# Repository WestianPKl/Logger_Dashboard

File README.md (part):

# 🌡️ IoT Logger Dashboard

A full-stack IoT monitoring platform for collecting, visualizing, and managing environmental sensor data from distributed devices. The system integrates custom-built hardware (ESP32, STM32, MicroPython nodes) with a modern web dashboard, communicating over MQTT and WebSockets for real-time data streaming.

---

## 📋 Table of Contents

- [Overview](#overview)
- [Architecture](#architecture)
- [Technology Stack](#technology-stack)
- [Features](#features)
- [Project Structure](#project-structure)
- [Backend](#backend)
- [Frontend](#frontend)
- [Logger Firmware](#logger-firmware)
- [Database](#database)
- [Authentication & Authorization](#authentication--authorization)
- [MQTT Communication](#mqtt-communication)
- [Hardware](#hardware)
- [Getting Started](#getting-started)
- [Environment Variables](#environment-variables)
- [API Reference](#api-reference)
- [Testing](#testing)

---

## Overview

IoT Logger Dashboard is designed to monitor environmental conditions (temperature, humidity, atmospheric pressure, altitude, voltage) across multiple locations. Sensor nodes deployed in buildings collect data and transmit it via MQTT to a centralized backend. Users interact with the system through a responsive web dashboard that provides real-time charts, floor plan visualizations, equipment management, and a full role-based administration panel.

**Key metrics:**

- 380+ tracked devices (loggers, sensors, relays)
- 247,000+ recorded measurements
- 12 measurement parameter types
- Multi-location, multi-floor support
- 90 concurrent database connections
- 4 JWT token types for layered security

---

## Architecture

```
┌──────────────────┐      MQTT       ┌──────────────────┐     HTTP/WS     ┌──────────────────┐
│   Sensor Nodes   │ ──────────────► │     Backend      │ ◄────────────── │    Frontend      │
│                  │                 │                  │ ──────────────► │                  │
│  ESP32 + STM32   │  devices/+/    │  Express.js 5.2  │   Socket.io     │  React 19 + TS   │
│  MicroPython     │  status        │  Sequelize ORM   │   4.8           │  MUI 7 + Redux   │
│  SHT40 / BME280  │                │  MQTT Client     │                 │  ECharts + XYFlow│
│  PCF8563T RTC    │  ◄──────────── │  Socket.io 4.8   │                 │  RTK Query       │
│                  │  devices/      │  Sharp + Multer  │                 │  Vite 7.3 (SWC)  │
│                  │  {id}/cmd      │  Nodemailer      │                 │                  │
└──────────────────┘                 └────────┬─────────┘                 └──────────────────┘
                                              │
                                     ┌────────▼─────────┐
                                     │   MySQL 9.x DB   │
                                     │  14 tables       │
                                     │  5 views         │
                                     │  Pool: 90 conn   │
                                     └──────────────────┘
```

---

## Technology Stack

### Backend

| Technology        | Version    | Purpose                                    |
| ----------------- | ---------- | ------------------------------------------ |
| Node.js           | ES Modules | Runtime environment                        |
| Express.js        | 5.2.1      | HTTP framework                             |
| Sequelize         | 6.37.7     | MySQL ORM with transactions & soft deletes |
| mysql2            | 3.16.1     | MySQL driver                               |
| Socket.io         | 4.8.3      | Real-time WebSocket communication          |
| MQTT.js           | 5.14.1     | IoT message broker client                  |
| JSON Web Token    | 9.0.3      | Authentication (4 token types)             |
| express-validator | 7.3.1      | Request body validation                    |
| bcryptjs          | 3.0.3      | Password hashing                           |
| Sharp             | 0.34.5     | Image processing & WebP conversion         |
| Multer            | 2.0.2      | File upload handling (500KB limit)         |
| Nodemailer        | 7.0.12     | Email via Gmail SMTP (password reset)      |
| Morgan            | 1.10.1     | HTTP access logging                        |
| Compression       | 1.8.1      | Gzip response compression                  |
| uuid              | 13.0.0     | Unique filename generation                 |
| dotenv            | 17.2.3     | Environment variable management            |
| Jest              | 30.2.0     | Testing framework                          |
| Supertest         | 7.2.2      | HTTP integration testing                   |
| ESLint + Prettier | —          | Code quality & formatting                  |

### Frontend

| Technology          | Version | Purpose                            |
| ------------------- | ------- | ---------------------------------- |
| React               | 19.2.3  | UI framework                       |
| TypeScript          | 5.9.3   | Type safety                        |
| Vite                | 7.3.1   | Build tool (SWC transpiler)        |
| Material UI (MUI)   | 7.3.7   | Component library                  |
| MUI X Data Grid     | 8.26.0  | Advanced sortable/paginated tables |
| Redux Toolkit       | 2.11.2  | State management with RTK Query    |
| React Redux         | 9.2.0   | React-Redux bindings               |
| React Router        | 7.13.0  | Client-side routing with loaders   |
| Socket.io Client    | 4.8.3   | Real-time device updates           |
| ECharts             | 3.0.6   | Time-series data visualization     |
| XYFlow (React Flow) | 12.10.0 | Graph / flow diagrams              |
| Styled Components   | 6.3.8   | CSS-in-JS styling                  |
| Emotion             | 11.14.0 | MUI styling engine                 |
| xlsx                | 0.18.5  | Excel spreadsheet generation       |
| file-saver          | 2.0.5   | Client-side file download          |
| jwt-decode          | 4.0.0   | Client-side JWT inspection         |

### Embedded / Logger

| Technology                        | Purpose                                      |
| --------------------------------- | -------------------------------------------- |
| ESP32 (MicroPython)               | Main IoT gateway — WiFi, MQTT, UART to STM32 |
| STM32L476RG / STM32F412RG (CMSIS) | Low-level sensor hub — bare-metal C with DMA |
| MicroPython (generic)             | Standalone sensor nodes — HTTP POST to API   |
| PlatformIO                        | STM32 build & flash toolchain                |
| KiCad                             | PCB schematic & layout design                |

### Sensors & Peripherals

| Component     | Type       | Measurements / Function                               |
| ------------- | ---------- | ----------------------------------------------------- |
| SHT30 / SHT40 | I2C sensor | Temperature (-40–125°C), Humidity (0–100%)            |
| BME280        | I2C sensor | Temperature, Humidity, Atmospheric Pressure, Altitude |
| PCF8563T      | I2C RTC    | Real-Time Clock with battery backup                   |
| I2C LCD       | Display    | Sensor readings & status display                      |
| RGB LEDs      | Output     | Status indication (PWM, 0–65535 range)                |
| Relay module  | Output     | 4-channel relay control (pins 12–15)                  |
| Buzzer        | Output     | Audible alerts on threshold breach                    |
| Push Buttons  | Input      | User interaction (debounced, long-press 3s)           |

---

## Features

- **Real-Time Monitoring** — Live sensor data via MQTT → Socket.io WebSocket pipeline with per-logger events
- **Interactive Charts** — Time-series visualization with ECharts, range selection, and XLSX export
- **Floor Plan Visualization** — Upload floor plan images, place loggers with x/y positioning and zoom control
- **Multi-Location Support** — Organize devices by house → floor → logger hierarchy
- **Equipment Inventory** — Full CRUD for loggers, sensors, relays with soft delete and restore
- **Device Telemetry** — Track firmware/hardware versions, serial numbers, build dates, IP address, last seen
- **Sensor Capability Mapping** — Many-to-many mapping of sensors to data definition parameters
- **Role-Based Access Control** — Three-dimensional permission matrix: functionality × object × access level
- **Superuser Override** — Superuser flag bypasses all permission checks
- **User Management** — Registration, login, avatar upload with Sharp WebP conversion, password reset via Gmail SMTP
- **Data Export** — Export sensor data to XLSX spreadsheets with pivot view support
- **Error Tracking** — Log device and system errors with type (Equipment/DB/Other) and severity (Critical→Info)
- **Equipment Event Logs** — Track STATUS, DATA, OTA, ERROR events per device
- **Process Management** — Define and manage operational process types and definitions
- **Audit Trail** — `created_by` / `updated_by` user tracking on all key entities
- **OTA Support** — Custom UART bootloader for STM32 firmware updates (app at `0x08008000`)
- **Service Mode** — ESP32 3-hour OTA window for configuration and firmware updates
- **Image Processing** — Automatic thumbnail generation and WebP conversion for avatars and floor plans
- **HTTP Access Logging** — Morgan combined-format logging to `access.log`
- **Gzip Compression** — Response compression via compression middleware
- **Transaction Safety** — Sequelize transactions with rollback on all write operations

---

## Project Structure

```
Logger_Dashboard/
│
├── backend/                    # Node.js Express API server
│   ├── server/
│   │   ├── app.js              # Express app setup, middleware, CORS
│   │   ├── mqttClient.js       # MQTT subscriber & data processing
│   │   ├── api/
│   │   │   ├── controller/     # Request handlers
│   │   │   ├── model/          # Sequelize models
│   │   │   └── routes/         # Express route definitions
│   │   ├── bin/www.js          # HTTP server bootstrap + Socket.io init
│   │   ├── libs/jwtToken.js    # JWT generation (4 token types)
│   │   ├── middleware/
│   │   │   ├── body-validation.js   # Request body validation
│   │   │   ├── file.js              # File upload handling (multer)
│   │   │   ├── jwtValidation.js     # JWT auth + permission checking
│   │   │   └── socket.js           # Socket.io middleware
│   │   └── util/
│   │       ├── database.js          # Sequelize connection config
│   │       ├── nodemailer.js        # Email transport setup
│   │       ├── responseHelper.js    # Standardized API responses
│   │       └── sequelizeTools.js    # Query builder utilities
│   ├── uploads/                # Uploaded files (avatars, floor plans)
│   ├── data.json               # Static configuration data
│   ├── package.json
│   ├── jest.config.js
│   └── eslint.config.js
│
├── frontend/                   # React SPA
│   ├── src/
│   │   ├── App.tsx             # Root component
│   │   ├── main.tsx            # Entry point
│   │   ├── components/         # Reusable UI components
│   │   │   ├── selectors/      # Equipment, sensor, house dropdowns
│   │   │   ├── ui/             # SnackBar, forms, modals
│   │   │   └── scripts/        # API interaction helpers
│   │   ├── modules/            # Feature modules (pages)
│   │   │   ├── admin/          # User/role/permission management
│   │   │   ├── dashboard/      # Real-time overview
│   │   │   ├── data/           # Charts, data tables, layout view
│   │   │   ├── equipment/      # Device inventory
│   │   │   ├── house/          # Location & floor management
│   │   │   ├── user/           # User profile
│   │   │   └── process/        # Process workflows
│   │   ├── router/             # SPA route configuration
│   │   ├── socket/             # Socket.io client setup
│   │   ├── store/              # Redux store (auth, account, app state)
│   │   └── util/               # Theme, API helpers, utilities
│   ├── dist-frontend/          # Production build output
│   ├── package.json
│   ├── vite.config.ts
│   └── tsconfig.json
│
├── logger/                     # Embedded firmware
│   ├── ESP32/                  # ESP32 MicroPython firmware
│   │   ├── main.py             # Boot: WiFi → NTP → MQTT → STM32
│   │   ├── program.py          # Main loop: status/data publishing
│   │   ├── mqtt_simple.py      # Lightweight MQTT client
│   │   ├── wireless.py         # WiFi + NTP connection manager
│   │   ├── stm32_uart.py       # UART bridge to STM32 (115200 baud)
│   │   ├── config.py           # Device configuration (IDs, WiFi, MQTT)
│   │   └── status.json         # Runtime status snapshot
│   ├── Micropython/            # Generic MicroPython sensor nodes
│   │   ├── main.py             # Sensor reading + HTTP POST loop
│   │   ├── config.py           # Node configuration
│   │   ├── sht30.py / sht40.py # Temperature/humidity drivers
│   │   ├── bme280_i2c.py       # Pressure/altitude driver
│   │   ├── i2c_lcd.py          # LCD display driver
│   │   ├── rtc_clock.py        # RTC time management
│   │   └── ...                 # Additional peripheral drivers
│   └── STM32/                  # STM32 bare-metal firmware (C / CMSIS)
│       ├── application/        # Main application (PlatformIO project)
│       │   └── src/            # adc, bme280, sht40, i2c, spi, uart,
│       │                       # lcd, rtc, pcf8563t, dma drivers
│       ├── bootloader/         # UART bootloader for OTA updates
│       │   └── src/            # main.c, uart.c, systick.c
│       ├── production_files/   # Flash programming scripts & binaries
│       ├── STM32F412RGT6/      # Reference docs & alt. target
│       └── STM32L4/            # Reference docs for L476RG
│
├── database/                   # Database setup
│   ├── db.sql                  # Schema: tables, views, indexes
│   └── db_data.sql             # Seed data (types, definitions, roles)
│
├── permissions/
│   └── permissions.json        # Default permission matrix
│
└── docs/                       # Documentation & hardware resources
    ├── LoggerDashboard.postman_collection.json  # API collection
    ├── Cover/PicoLogger/       # 3D-printable enclosures (.stl)
    └── PCB/PicoLogger/         # KiCad PCB designs
        ├── IoT_Logger_B_1.0/
        ├── IoT_Logger_C_1.0/
        ├── Pico_TH_Logger_SMD_PCF8563T_2.1/
        └── Pico_TH_Logger_Relay_SMD_PCF8563T_2.1/
```

---

## Backend

### Express API Server

The backend is a Node.js Express 5.2 server with ES module support. It provides a RESTful API, handles MQTT message ingestion from IoT devices, and broadcasts real-time updates to connected clients via Socket.io.

**Middleware stack (in order):**

1. **CORS** — Configurable origins via `FRONTEND_ORIGIN` env var (comma-separated)
2. **Compression** — Gzip response compression
3. **Morgan** — HTTP access logging (combined format → `access.log`)
4. **Express JSON/URL-encoded** — Body parsing with 10MB limit
5. **Cookie Parser** — Cookie handling
6. **Static Files** — Serves `/uploads` and frontend build (`dist-frontend/`)
7. **JWT Validation** — Bearer token verification on protected routes
8. **Permission Checking** — Granular RBAC enforcement per endpoint

**Route mounting:**

| Mount Path       | Module     |
| ---------------- | ---------- |
| `/api/user`      | User       |
| `/api/data`      | Data       |
| `/api/equipment` | Equipment  |
| `/api/process`   | Process    |
| `/api/house`     | House      |
| `/api/common`    | Error Logs |
| `/api/mqtt`      | MQTT       |
| `/api/adm`       | Admin      |

**Error handling:**

- 404 → `notFound()` for unknown routes
- Global error handler → `internalServerError()`
- In production, unknown routes serve `index.html` (SPA fallback)

**Standardized API response format:**

```json
{
	"success": true,
	"message": "Description of result",
	"data": {}
}
```

**HTTP status code helpers:** `200`, `201`, `204`, `400`, `401`, `403`, `404`, `409`, `422`, `429`, `500`, `503`

### File Upload & Image Processing

| Setting       | Value                                              |
| ------------- | -------------------------------------------------- |
| Max file size | 500 KB                                             |
| MIME types    | `image/png`, `image/jpeg`, `image/jpg`             |
| Storage       | `uploads/` directory                               |
| Filename      | `${uuid()}.${extension}`                           |
| Processing    | Sharp — auto WebP conversion, thumbnail generation |

Image variants stored:

- **Avatars:** `avatar` (thumbnail) + `avatar_big` (full-size)
- **House pictures:** `picture_link` + `picture_link_big`
- **Floor layouts:** `layout` (small) + `layout_big` (full-size)

### MQTT Data Pipeline

When sensor data arrives over MQTT:

1. Message is parsed from the `devices/+/status` topic (QoS 0)
2. Message type is identified: `DATA`, `STATUS`, `ERROR`, or `OTA`
3. Timestamps are normalized to `Europe/Warsaw` timezone (UTC+1/+2)
4. **For DATA messages:**
   - SHT40 readings extracted → `temperature`, `humidity`
   - BME280 readings extracted → `temperature`, `humidity`, `pressure` → `atmPressure`, `altitude`
   - Voltage readings extracted → `vin` array → individual voltage values
   - Each measurement matched to `DataDefinition` by name
   - `DataLogs` record created with value + timestamp
   - `DataLastValue` cache replaced with latest reading
5. **For all messages:** `EquStats` updated (firmware versions, serial numbers, build dates, IP, `last_seen`)
6. Socket.io emits `logger_${loggerId}` event with `'refresh'` payload
7. **For ERROR messages:** `ErrorLog` record created in database

**MQTT connection config:**

```
Reconnect period: 2000ms
Keep-alive: 30s
Clean session: true
```

---

## Frontend

### React SPA

The frontend is a single-page application built with React 19, TypeScript, and Material UI 7. It uses Redux Toolkit with RTK Query for API calls and Socket.io for real-time updates.

**State management (Redux store slices):**

- `accountSlice` — User profile data, avatar
- `authenticateSlice` — JWT tokens, login state, permissions
- `applicationSlice` — Global UI state (snackbar alerts, loading indicators)
- `api` — RTK Query endpoints with auto-caching and tag-based invalidation

**RTK Query features:**

- Auto Bearer token injection from localStorage
- 401 error handling → automatic logout + redirect to `/login`
- Zero retry policy (`maxRetries: 0`)
- Cache tags: User, Equipment, House, Data, Admin (14 tag types)

**Socket.io client:**

- Timeout: 5000ms, reconnection attempts: 3, delay: 1000ms
- Listens to `logger_${loggerId}` events for per-device data refresh

### Routes & Pages

```
/ ........................... Main menu
/login ...................... Login page
/register ................... Registration page
/logout ..................... Logout action
/password-reset ............. Request password reset email
/password-reset/:token ...... Complete password reset

/house ...................... House management
  /house/houses ............. House list & CRUD
  /house/floors ............. Floor list & CRUD
  /house/loggers ............ Logger placement management
/house-details/:houseId ..... Floor plan viewer with logger positions

/equipment .................. Equipment inventory
  Types, vendors, models, equipment CRUD
  Equipment log viewer

/logs/:equLoggerId .......... Equipment event log

/data ....................... Data module
  /data ..................... Data summary & definitions
  /data/data-logger/:id ..... Time-series chart view (ECharts)

/admin-panel ................ Administration
  Functionality, object, access level definitions
  Role & permission management
  User management

/user ....................... User module
  Profile, permissions view, roles
```

**Module views:**

| Module            | Description                                                                      |
| ----------------- | -------------------------------------------------------------------------------- |
| **Dashboard**     | Real-time overview cards with latest device readings                             |
| **Data**          | Time-series charts (ECharts), pivot tables, XLSX export, layout visualization    |
| **Equipment**     | CRUD for devices, vendors, models, types; soft delete/restore; event logs        |
| **House**         | Location CRUD, floor plans with image upload, interactive logger placement       |
| **House Details** | Floor plan viewer with logger positions, floor tree navigation, edit forms       |
| **Admin**         | Functionality/object/access level definitions, role CRUD, permission matrix      |
| **User**          | Login, registration, profile with avatar upload, password reset, permission view |
| **Process**       | Process type & definition management                                             |

### Reusable Components

**18 Select dropdowns:** `HouseSelect`, `HouseFloorSelect`, `EquipmentSelect`, `EquipmentVendorSelect`, `EquipmentTypeSelect`, `EquipmentModelSelect`, `EquipmentLoggerSelect`, `EquipmentSensorSelect`, `DataDefinitionSelect`, `AdminUserSelect`, `AdminAccessLevelSelect`, `AdminFunctionalityDefinitionSelect`, `AdminObjectDefinitionSelect`, and more.

**UI components:** `SnackBar` (alert notifications), `LoadingCircle` (spinner), `Wrapper` (layout), `TabPanel` (tabbed content).

---

## Logger Firmware

### ESP32 (MicroPython) — IoT Gateway

The ESP32 acts as the main IoT gateway, bridging STM32 sensor hardware to the cloud. On boot it:

1. Configures GPIO pins (status LED, STM32 control, power LED)
2. Initializes I2C bus for sensor modules and LCD
3. Connects to WiFi (up to 20 retries, 1s each)
4. Synchronizes time via NTP (UTC+1, max 10 retries)
5. Initializes MQTT connection to the broker
6. Establishes UART communication with the STM32 (115200 baud)
7. Enters the main loop publishing status and sensor data

**GPIO Configuration:**

| Pin | Function          | Mode              |
| --- | ----------------- | ----------------- |
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
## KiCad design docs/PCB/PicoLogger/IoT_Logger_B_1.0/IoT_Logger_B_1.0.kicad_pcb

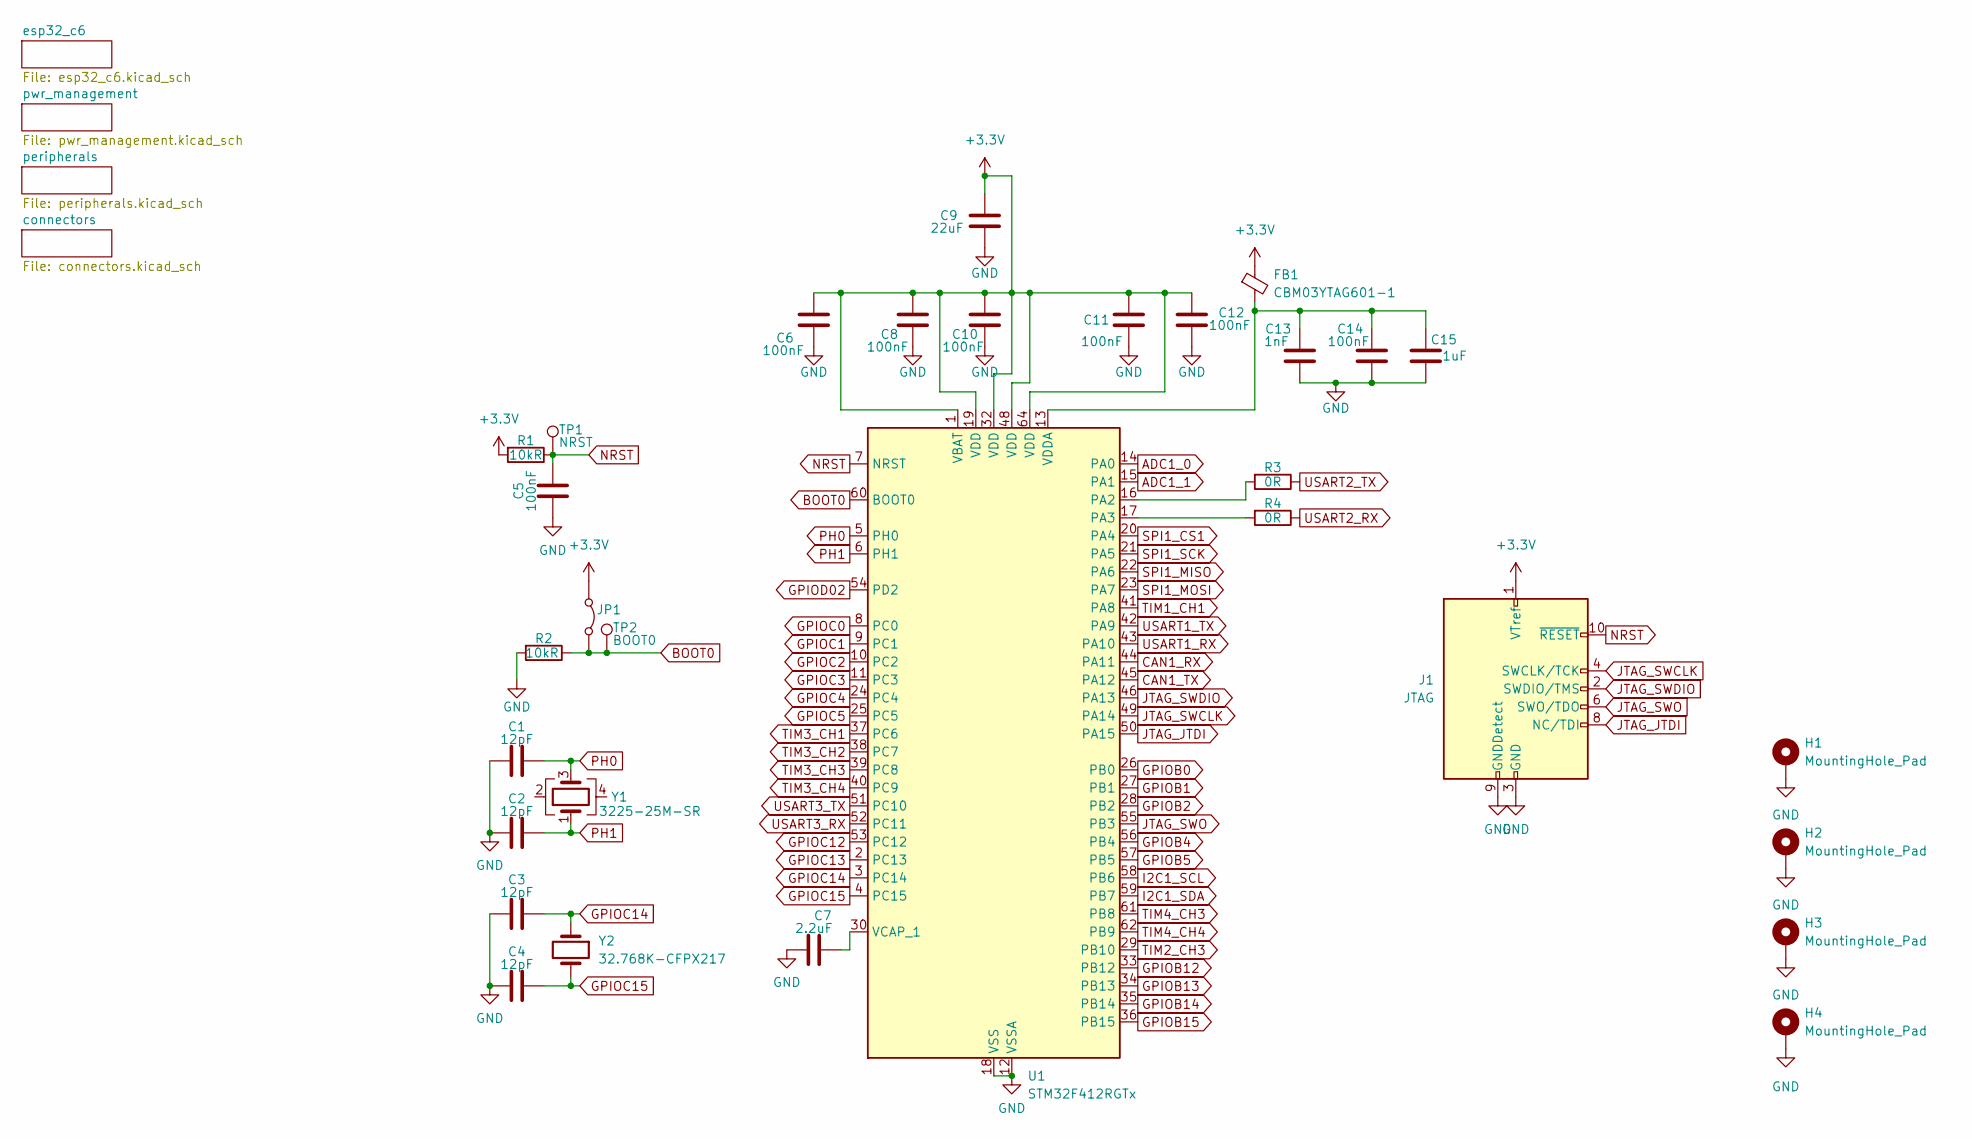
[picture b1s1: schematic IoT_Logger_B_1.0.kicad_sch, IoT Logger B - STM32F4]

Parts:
C1, C2, C3, C4: 12pF; C_0603_1608Metric
C5, C6, C8, C10, C11, C12, C14: 100nF; C_0603_1608Metric
C7: 2.2uF; C_0603_1608Metric
C9: 22uF; C_0603_1608Metric
C13: 1nF; C_0603_1608Metric
C15: 1uF; C_0603_1608Metric
FB1: CBM03YTAG601-1; L_0603_1608Metric
H1, H2, H3, H4: MountingHole_Pad; MountingHole_3.2mm_M3_DIN965_Pad
J1: JTAG; PinHeader_2x05_P1.27mm_Vertical
JP1: Jumper_2_Bridged; PinHeader_1x02_P2.54mm_Vertical
R1, R2: 10kR; R_0603_1608Metric
R3, R4: 0R; R_0603_1608Metric
TP1: NRST; TestPoint_Pad_D1.5mm
TP2: BOOT0; TestPoint_Pad_D1.5mm
U1: STM32F412RGTx; LQFP-64_10x10mm_P0.5mm
Y1: 3225-25M-SR; Crystal_SMD_3225-4Pin_3.2x2.5mm
Y2: 32.768K-CFPX217; Crystal_SMD_3215-2Pin_3.2x1.5mm

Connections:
+3.3V: C6.1, C8.1, C9.1, C10.1, C11.1, C12.1, FB1.1, J1.1 (VTref), JP1.1 (A), R1.2, U1.1 (VBAT), U1.19 (VDD), U1.32 (VDD), U1.48 (VDD), U1.64 (VDD); also elsewhere on the board
ADC1_0: U1.14 (PA0); also elsewhere on the board
ADC1_1: U1.15 (PA1); also elsewhere on the board
BOOT0: JP1.2 (B), R2.1, TP2.1, U1.60 (BOOT0); also elsewhere on the board
CAN1_RX: U1.44 (PA11); also elsewhere on the board
CAN1_TX: U1.45 (PA12); also elsewhere on the board
GND: C1.1, C2.1, C3.1, C4.1, C5.1, C6.2, C7.1, C8.2, C9.2, C10.2, C11.2, C12.2, C13.2, C14.2, C15.2, H1.1, H2.1, H3.1, H4.1, J1.3 (GND), J1.5 (GND), J1.9 (GNDDetect), R2.2, U1.12 (VSSA), U1.18 (VSS), U1.31 (VSS), U1.47 (VSS), U1.63 (VSS); also elsewhere on the board
GPIOB0: U1.26 (PB0); also elsewhere on the board
GPIOB1: U1.27 (PB1); also elsewhere on the board
GPIOB2: U1.28 (PB2); also elsewhere on the board
GPIOB4: U1.56 (PB4)
GPIOB5: U1.57 (PB5); also elsewhere on the board
GPIOB12: U1.33 (PB12); also elsewhere on the board
GPIOB13: U1.34 (PB13); also elsewhere on the board
GPIOB14: U1.35 (PB14); also elsewhere on the board
GPIOB15: U1.36 (PB15); also elsewhere on the board
GPIOC0: U1.8 (PC0); also elsewhere on the board
GPIOC1: U1.9 (PC1); also elsewhere on the board
GPIOC2: U1.10 (PC2); also elsewhere on the board
GPIOC3: U1.11 (PC3); also elsewhere on the board
GPIOC4: U1.24 (PC4); also elsewhere on the board
GPIOC5: U1.25 (PC5); also elsewhere on the board
GPIOC12: U1.53 (PC12); also elsewhere on the board
GPIOC13: U1.2 (PC13); also elsewhere on the board
GPIOC14: C3.2, U1.3 (PC14), Y2.1
GPIOC15: C4.2, U1.4 (PC15), Y2.2
GPIOD02: U1.54 (PD2)
I2C1_SCL: U1.58 (PB6); also elsewhere on the board
I2C1_SDA: U1.59 (PB7); also elsewhere on the board
JTAG_JTDI: J1.8 (NC/TDI), U1.50 (PA15)
JTAG_SWCLK: J1.4 (SWCLK/TCK), U1.49 (PA14)
JTAG_SWDIO: J1.2 (SWDIO/TMS), U1.46 (PA13)
JTAG_SWO: J1.6 (SWO/TDO), U1.55 (PB3)
NRST: C5.2, J1.10 (~RESET), R1.1, TP1.1, U1.7 (NRST); also elsewhere on the board
unnamed: R3.2, U1.16 (PA2)
unnamed: R4.2, U1.17 (PA3)
unnamed: C7.2, U1.30 (VCAP_1)
unnamed: C13.1, C14.1, C15.1, FB1.2, U1.13 (VDDA)
PH0: C1.2, U1.5 (PH0), Y1.3
PH1: C2.2, U1.6 (PH1), Y1.1
SPI1_CS1: U1.20 (PA4); also elsewhere on the board
SPI1_MISO: U1.22 (PA6); also elsewhere on the board
SPI1_MOSI: U1.23 (PA7); also elsewhere on the board
SPI1_SCK: U1.21 (PA5); also elsewhere on the board
TIM1_CH1: U1.41 (PA8); also elsewhere on the board
TIM2_CH3: U1.29 (PB10); also elsewhere on the board
TIM3_CH1: U1.37 (PC6); also elsewhere on the board
TIM3_CH2: U1.38 (PC7); also elsewhere on the board
TIM3_CH3: U1.39 (PC8); also elsewhere on the board
TIM3_CH4: U1.40 (PC9); also elsewhere on the board
TIM4_CH3: U1.61 (PB8); also elsewhere on the board
TIM4_CH4: U1.62 (PB9); also elsewhere on the board
USART1_RX: U1.43 (PA10); also elsewhere on the board
USART1_TX: U1.42 (PA9); also elsewhere on the board
USART2_RX: R4.1; also elsewhere on the board
USART2_TX: R3.1; also elsewhere on the board
USART3_RX: U1.52 (PC11)
USART3_TX: U1.51 (PC10)

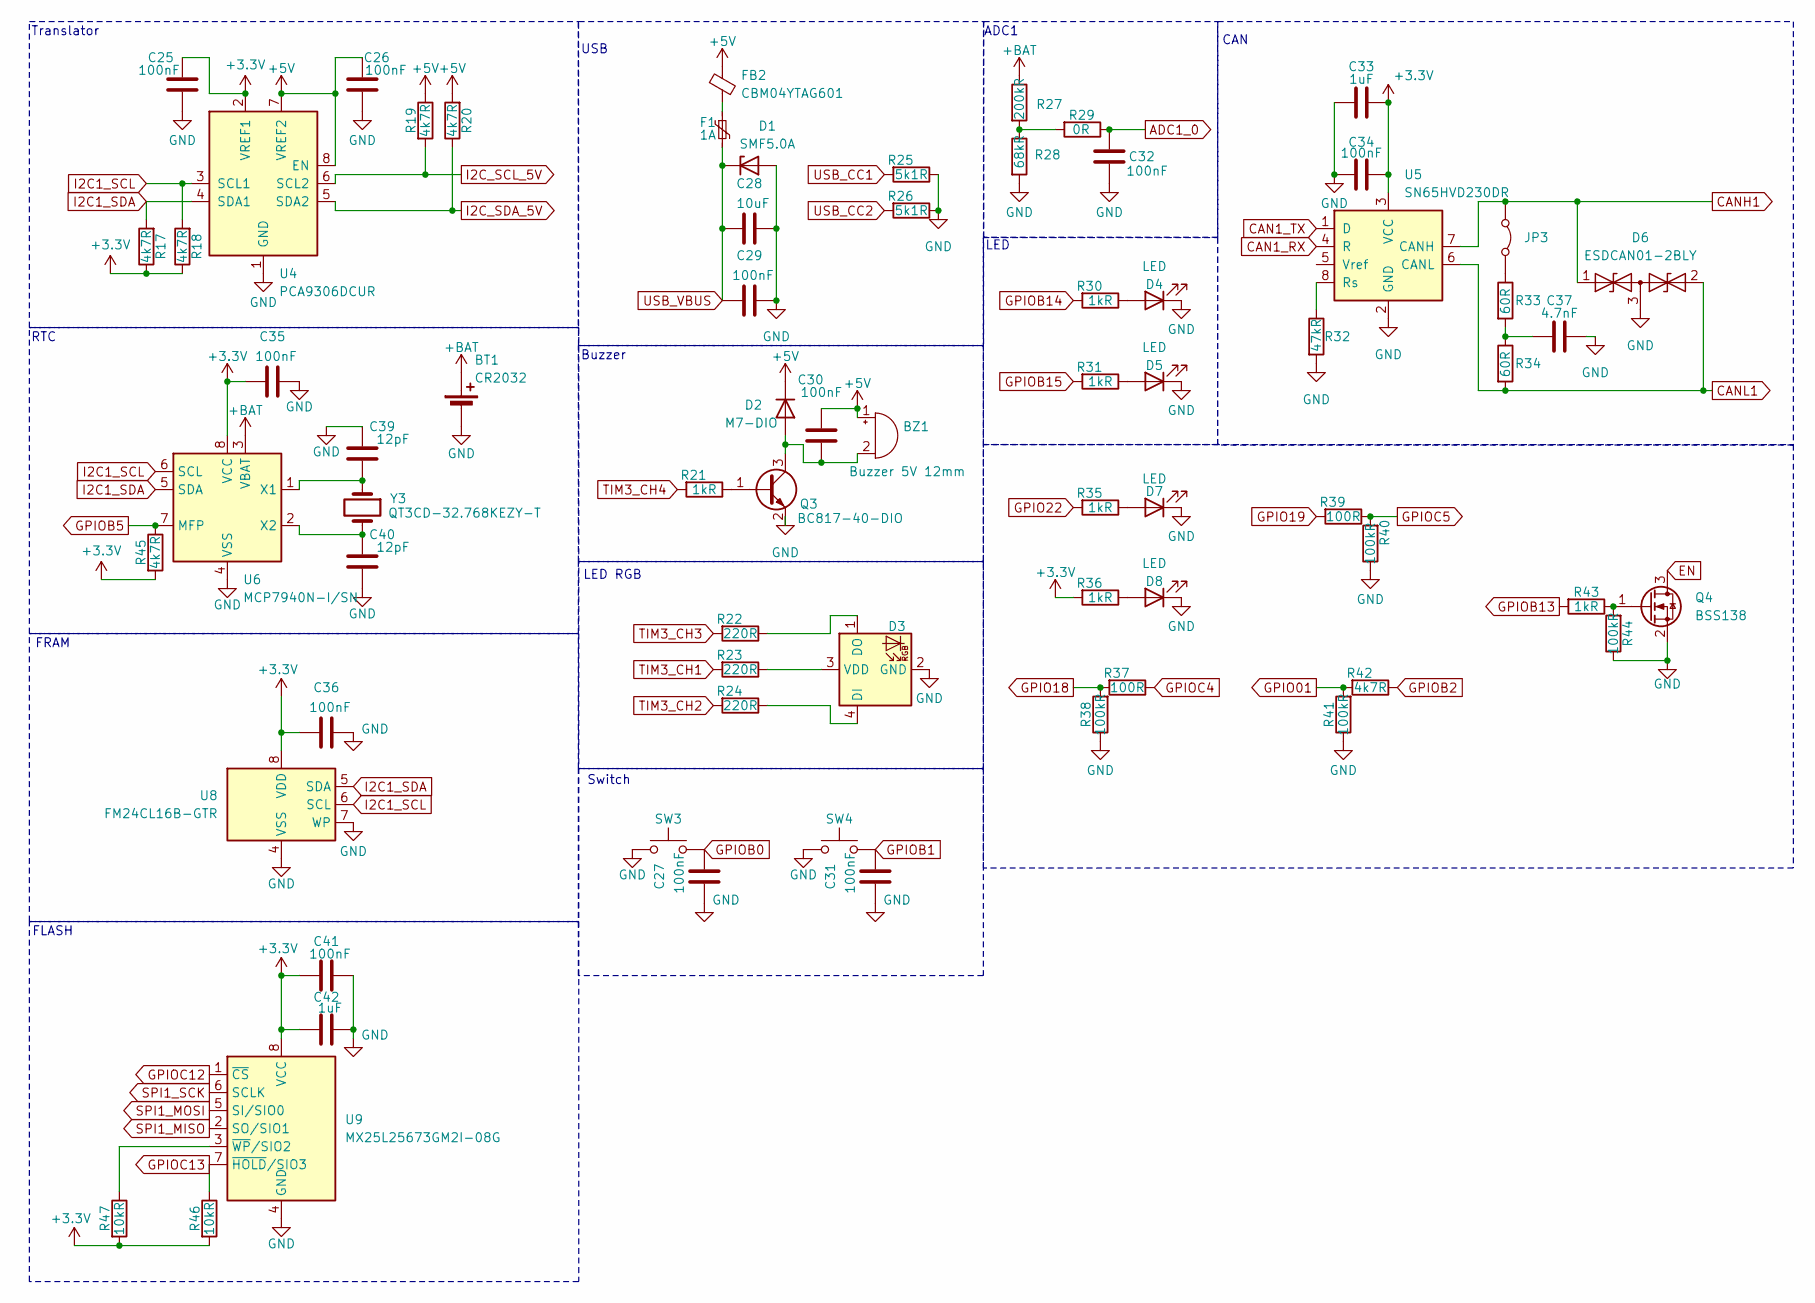
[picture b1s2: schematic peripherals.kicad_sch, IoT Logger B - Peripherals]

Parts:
BT1: CR2032; BatteryHolder_Keystone_1060_1x2032
BZ1: Buzzer 5V 12mm; Buzzer_12x9.5RM7.6
C25, C26, C27, C29, C30, C31, C32, C34, C35, C36, C41: 100nF; C_0603_1608Metric
C28: 10uF; C_0603_1608Metric
C33, C42: 1uF; C_0603_1608Metric
C37: 4.7nF; C_0603_1608Metric
C39, C40: 12pF; C_0603_1608Metric
D1: SMF5.0A; D_SOD-123F
D2: M7-DIO; D_SMA
D3: OSTBPCS2C2B; LED_Avago_PLCC4_3.2x2.8mm_CW
D4, D5, D7, D8: LED; LED_0603_1608Metric
D6: ESDCAN01-2BLY; SOT-23
F1: 1A; Fuse_1206_3216Metric
FB2: CBM04YTAG601; L_1206_3216Metric
JP3: Jumper_2_Bridged; PinHeader_1x02_P2.54mm_Vertical
Q3: BC817-40-DIO; SOT-23
Q4: BSS138; SOT-23
R17, R18, R19, R20, R42, R45: 4k7R; R_0603_1608Metric
R21, R30, R31, R35, R36, R43: 1kR; R_0603_1608Metric
R22, R23, R24: 220R; R_0603_1608Metric
R25, R26: 5k1R; R_0603_1608Metric
R27: 200kR; R_0603_1608Metric
R28: 68kR; R_0603_1608Metric
R29: 0R; R_0603_1608Metric
R32: 47kR; R_0603_1608Metric
R33, R34: 60R; R_0603_1608Metric
R37, R39: 100R; R_0603_1608Metric
R38, R40, R41, R44: 100kR; R_0603_1608Metric
R46, R47: 10kR; R_0603_1608Metric
SW3, SW4: Tact Switch 6x6mm / 13mm; SW_PUSH_6mm
U4: PCA9306DCUR; VSSOP-8_2.3x2mm_P0.5mm
U5: SN65HVD230DR; SOIC-8_3.9x4.9mm_P1.27mm
U6: MCP7940N-I/SN; SOIC-8_3.9x4.9mm_P1.27mm
U8: FM24CL16B-GTR; SOIC-8_3.9x4.9mm_P1.27mm
U9: MX25L25673GM2I-08G; SOIC-8_5.3x5.3mm_P1.27mm
Y3: QT3CD-32.768KEZY-T; Crystal_SMD_3215-2Pin_3.2x1.5mm

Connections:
+3.3V: C25.1, C33.1, C34.1, C35.2, C36.2, C41.2, C42.2, R17.1, R18.1, R36.2, R45.2, R46.2, R47.2, U4.2 (VREF1), U5.3 (VCC), U6.8 (VCC), U8.8 (VDD), U9.8 (VCC); also elsewhere on the board
+5V: BZ1.1 (+), C26.1, C30.2, D2.1 (K), FB2.1, R19.1, R20.2, U4.7 (VREF2), U4.8 (EN); also elsewhere on the board
+BAT: BT1.1 (+), R27.1, U6.3 (VBAT)
ADC1_0: C32.1, R29.1; also elsewhere on the board
CAN1_RX: U5.4 (R); also elsewhere on the board
CAN1_TX: U5.1 (D); also elsewhere on the board
CANH1: D6.1 (A1), JP3.1 (A), U5.7 (CANH); also elsewhere on the board
CANL1: D6.2 (A2), R34.2, U5.6 (CANL); also elsewhere on the board
EN: Q4.3 (D); also elsewhere on the board
GND: BT1.2 (-), C25.2, C26.2, C27.2, C28.1, C29.1, C31.2, C32.2, C33.2, C34.2, C35.1, C36.1, C37.1, C39.2, C40.1, C41.1, C42.1, D1.2 (A), D3.2 (GND), D4.1 (K), D5.1 (K), D6.3 (common), D7.1 (K), D8.1 (K), Q3.2 (E), Q4.2 (S), R25.1, R26.1, R28.2, R32.2, R38.1, R40.1, R41.1, R44.1, SW3.1, SW4.1, U4.1 (GND), U5.2 (GND), U6.4 (VSS), U8.4 (VSS), U8.7 (WP), U9.4 (GND); also elsewhere on the board
GPIO01: R41.2, R42.2; also elsewhere on the board
GPIO18: R37.2, R38.2; also elsewhere on the board
GPIO19: R39.2; also elsewhere on the board
GPIO22: R35.2; also elsewhere on the board
GPIOB0: C27.1, SW3.2; also elsewhere on the board
GPIOB1: C31.1, SW4.2; also elsewhere on the board
GPIOB2: R42.1; also elsewhere on the board
GPIOB5: R45.1, U6.7 (MFP); also elsewhere on the board
GPIOB13: R43.2; also elsewhere on the board
GPIOB14: R30.2; also elsewhere on the board
GPIOB15: R31.2; also elsewhere on the board
GPIOC4: R37.1; also elsewhere on the board
GPIOC5: R39.1, R40.2; also elsewhere on the board
GPIOC12: U9.1 (~CS); also elsewhere on the board
GPIOC13: R46.1, U9.7 (~HOLD/SIO3); also elsewhere on the board
I2C1_SCL: R18.2, U4.3 (SCL1), U6.6 (SCL), U8.6 (SCL); also elsewhere on the board
I2C1_SDA: R17.2, U4.4 (SDA1), U6.5 (SDA), U8.5 (SDA); also elsewhere on the board
I2C_SCL_5V: R19.2, U4.6 (SCL2); also elsewhere on the board
I2C_SDA_5V: R20.1, U4.5 (SDA2); also elsewhere on the board
unnamed: BZ1.2 (-), C30.1, D2.2 (A), Q3.3 (C)
unnamed: C37.2, R33.2, R34.1
unnamed: D3.4 (DI), R24.1
unnamed: D3.1 (DO), R22.1
unnamed: D3.3 (VDD), R23.1
unnamed: D4.2 (A), R30.1
unnamed: D5.2 (A), R31.1
unnamed: D7.2 (A), R35.1
unnamed: D8.2 (A), R36.1
unnamed: F1.1, FB2.2
unnamed: JP3.2 (B), R33.1
unnamed: Q3.1 (B), R21.1
unnamed: Q4.1 (G), R43.1, R44.2
unnamed: R27.2, R28.1, R29.2
unnamed: R32.1, U5.8 (Rs)
unnamed: C39.1, U6.1 (X1), Y3.1
unnamed: C40.2, U6.2 (X2), Y3.2
unnamed: R47.1, U9.3 (~WP/SIO2)
SPI1_MISO: U9.2 (SO/SIO1); also elsewhere on the board
SPI1_MOSI: U9.5 (SI/SIO0); also elsewhere on the board
SPI1_SCK: U9.6 (SCLK); also elsewhere on the board
TIM3_CH1: R23.2; also elsewhere on the board
TIM3_CH2: R24.2; also elsewhere on the board
TIM3_CH3: R22.2; also elsewhere on the board
TIM3_CH4: R21.2; also elsewhere on the board
USB_CC1: R25.2; also elsewhere on the board
USB_CC2: R26.2; also elsewhere on the board
USB_VBUS: C28.2, C29.2, D1.1 (K), F1.2; also elsewhere on the board

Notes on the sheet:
USB
CAN
Switch
FRAM
Translator
Buzzer
FLASH
LED RGB
RTC
ADC1
LED

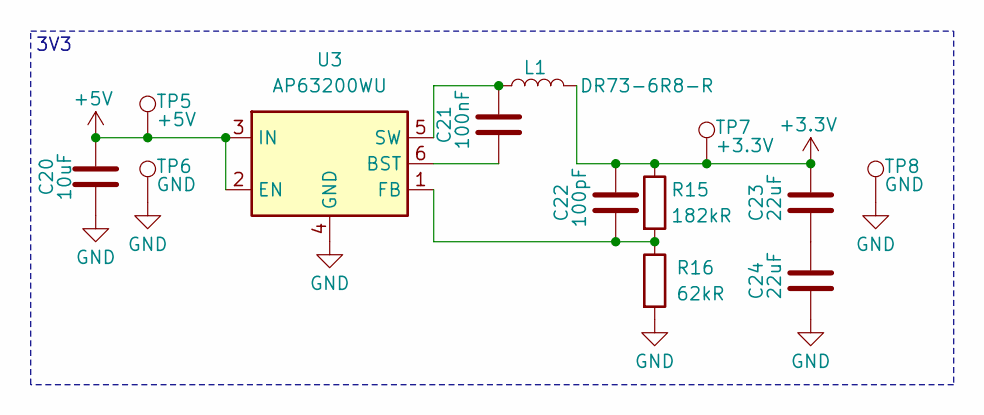
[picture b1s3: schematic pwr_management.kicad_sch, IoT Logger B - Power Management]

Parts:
C20: 10uF; C_1206_3216Metric
C21: 100nF; C_0805_2012Metric
C22: 100pF; C_0805_2012Metric
C23, C24: 22uF; C_1206_3216Metric
L1: DR73-6R8-R; L_7.3x7.3_H3.5
R15: 182kR; R_0805_2012Metric
R16: 62kR; R_0805_2012Metric
TP5: +5V; TestPoint_Pad_D1.5mm
TP6, TP8: GND; TestPoint_Pad_D1.5mm
TP7: +3.3V; TestPoint_Pad_D1.5mm
U3: AP63200WU; TSOT-23-6

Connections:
+3.3V: C22.1, C23.1, L1.2, R15.1, TP7.1; also elsewhere on the board
+5V: C20.1, TP5.1, U3.2 (EN), U3.3 (IN); also elsewhere on the board
GND: C20.2, C24.2, R16.2, TP6.1, TP8.1, U3.4 (GND); also elsewhere on the board
unnamed: C23.2, C24.1
unnamed: C21.2, U3.6 (BST)
unnamed: C22.2, R15.2, R16.1, U3.1 (FB)
unnamed: C21.1, L1.1, U3.5 (SW)

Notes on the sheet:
3V3

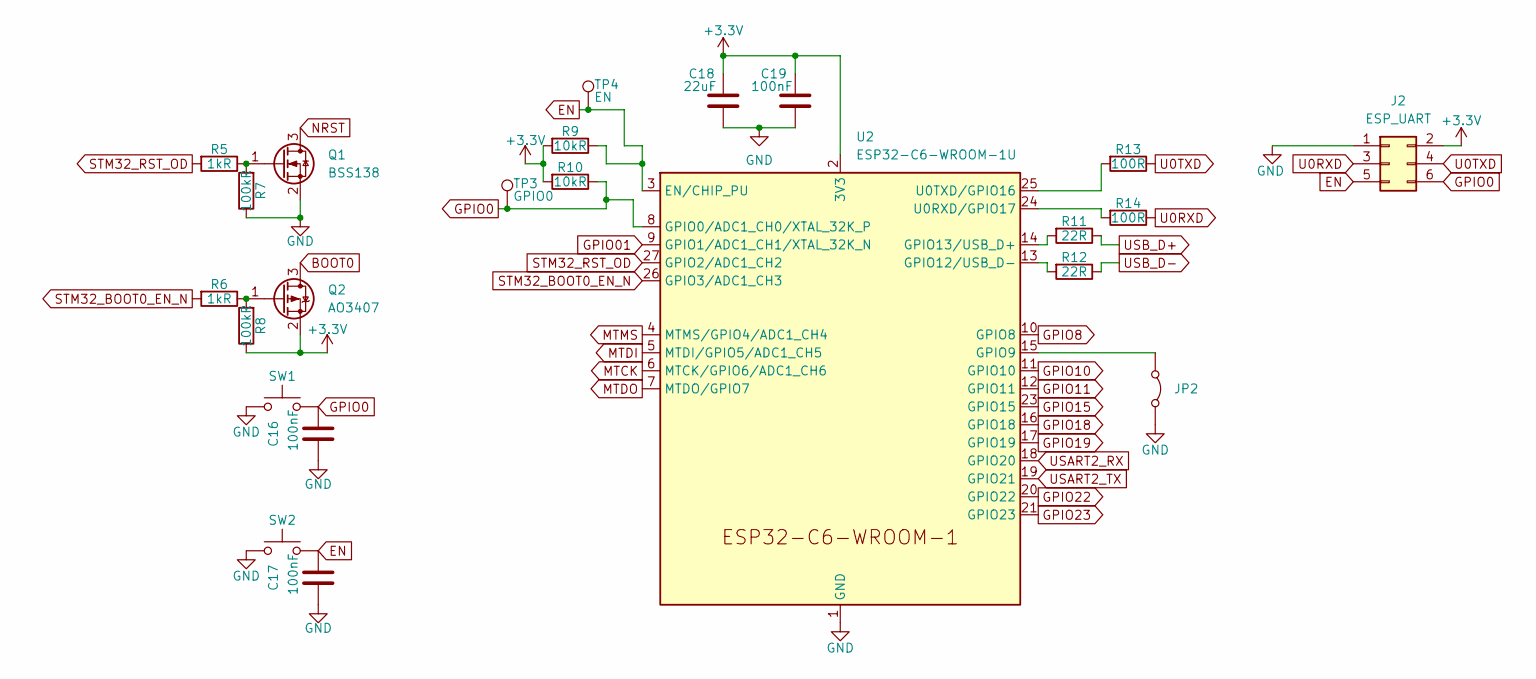
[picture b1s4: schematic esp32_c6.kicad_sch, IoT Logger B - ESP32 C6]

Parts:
C16, C17, C19: 100nF; C_0603_1608Metric
C18: 22uF; C_0603_1608Metric
J2: ESP_UART; PinHeader_2x03_P1.27mm_Vertical
JP2: Jumper_2_Bridged; PinHeader_1x02_P2.54mm_Vertical
Q1: BSS138; SOT-23
Q2: AO3407; SOT-23
R5, R6: 1kR; R_0603_1608Metric
R7, R8: 100kR; R_0603_1608Metric
R9, R10: 10kR; R_0603_1608Metric
R11, R12: 22R; R_0603_1608Metric
R13, R14: 100R; R_0603_1608Metric
SW1, SW2: Tact Switch 6x6mm / 13mm; SW_PUSH_6mm
TP3: GPIO0; TestPoint_Pad_D1.5mm
TP4: EN; TestPoint_Pad_D1.5mm
U2: ESP32-C6-WROOM-1U

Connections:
+3.3V: C18.1, C19.1, J2.2, Q2.2 (S), R8.1, R9.2, R10.2, U2.2 (3V3); also elsewhere on the board
BOOT0: Q2.3 (D); also elsewhere on the board
EN: C17.1, J2.5, R9.1, SW2.2, TP4.1, U2.3 (EN/CHIP_PU); also elsewhere on the board
GND: C16.2, C17.2, C18.2, C19.2, J2.1, JP2.2 (B), Q1.2 (S), R7.1, SW1.1, SW2.1, U2.1 (GND), U2.28 (GND), U2.29 (GND); also elsewhere on the board
GPIO0: C16.1, J2.6, R10.1, SW1.2, TP3.1, U2.8 (GPIO0/ADC1_CH0/XTAL_32K_P)
GPIO01: U2.9 (GPIO1/ADC1_CH1/XTAL_32K_N); also elsewhere on the board
GPIO8: U2.10 (GPIO8)
GPIO10: U2.11 (GPIO10)
GPIO11: U2.12 (GPIO11)
GPIO15: U2.23 (GPIO15)
GPIO18: U2.16 (GPIO18); also elsewhere on the board
GPIO19: U2.17 (GPIO19); also elsewhere on the board
GPIO22: U2.20 (GPIO22); also elsewhere on the board
GPIO23: U2.21 (GPIO23)
MTCK: U2.6 (MTCK/GPIO6/ADC1_CH6)
MTDI: U2.5 (MTDI/GPIO5/ADC1_CH5)
MTDO: U2.7 (MTDO/GPIO7)
MTMS: U2.4 (MTMS/GPIO4/ADC1_CH4)
NRST: Q1.3 (D); also elsewhere on the board
unnamed: JP2.1 (A), U2.15 (GPIO9)
unnamed: Q1.1 (G), R5.1, R7.2
unnamed: Q2.1 (G), R6.1, R8.2
unnamed: R12.2, U2.13 (GPIO12/USB_D-)
unnamed: R11.2, U2.14 (GPIO13/USB_D+)
unnamed: R14.2, U2.24 (U0RXD/GPIO17)
unnamed: R13.2, U2.25 (U0TXD/GPIO16)
STM32_BOOT0_EN_N: R6.2, U2.26 (GPIO3/ADC1_CH3)
STM32_RST_OD: R5.2, U2.27 (GPIO2/ADC1_CH2)
U0RXD: J2.3, R14.1
U0TXD: J2.4, R13.1
USART2_RX: U2.18 (GPIO20); also elsewhere on the board
USART2_TX: U2.19 (GPIO21); also elsewhere on the board
USB_D+: R11.1; also elsewhere on the board
USB_D-: R12.1; also elsewhere on the board

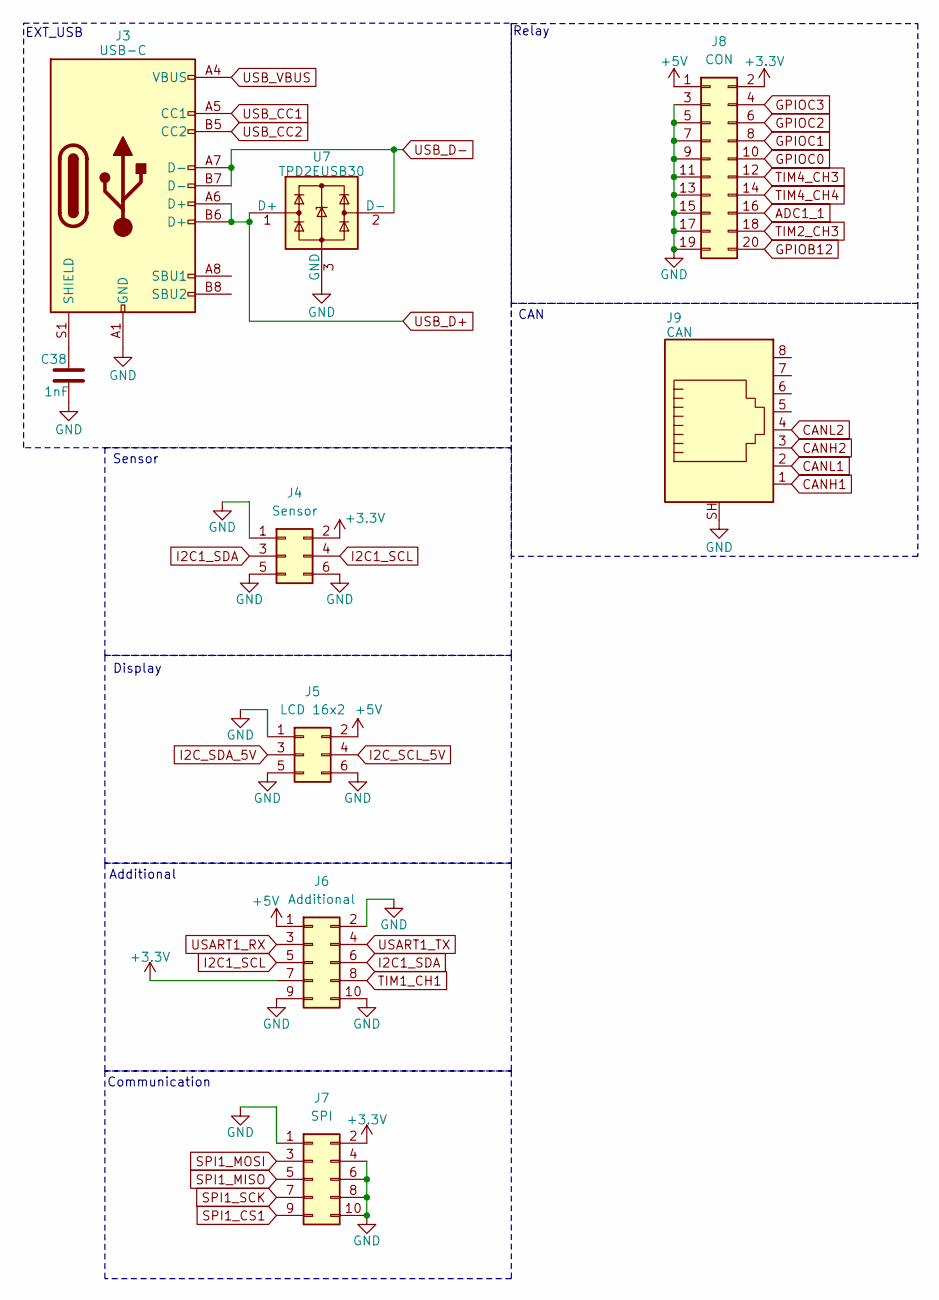
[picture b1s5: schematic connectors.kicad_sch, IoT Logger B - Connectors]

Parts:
C38: 1nF; C_0603_1608Metric
J3: USB-C; USB_C_Receptacle_GCT_USB4085
J4: Sensor; IDC-Header_2x03_P2.54mm_Vertical
J5: LCD 16x2; IDC-Header_2x03_P2.54mm_Vertical
J6: Additional; PinSocket_2x05_P2.54mm_Vertical
J7: SPI; IDC-Header_2x05_P2.54mm_Vertical
J8: CON; PinSocket_2x10_P2.54mm_Vertical
J9: CAN; RJ45_Amphenol_RJHSE5380_SHORT
U7: TPD2EUSB30; Texas_DRT-3

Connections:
+3.3V: J4.2, J6.7, J7.2, J8.2; also elsewhere on the board
+5V: J5.2, J6.1, J8.1; also elsewhere on the board
ADC1_1: J8.16; also elsewhere on the board
CANH1: J9.1; also elsewhere on the board
CANH2: J9.3
CANL1: J9.2; also elsewhere on the board
CANL2: J9.4
GND: C38.2, J3.A1 (GND), J3.A12 (GND), J3.B1 (GND), J3.B12 (GND), J4.1, J4.5, J4.6, J5.1, J5.5, J5.6, J6.2, J6.9, J6.10, J7.1, J7.4, J7.6, J7.8, J7.10, J8.3, J8.5, J8.7, J8.9, J8.11, J8.13, J8.15, J8.17, J8.19, J9.SH, U7.3 (GND); also elsewhere on the board
GPIOB12: J8.20; also elsewhere on the board
GPIOC0: J8.10; also elsewhere on the board
GPIOC1: J8.8; also elsewhere on the board
GPIOC2: J8.6; also elsewhere on the board
GPIOC3: J8.4; also elsewhere on the board
I2C1_SCL: J4.4, J6.5; also elsewhere on the board
I2C1_SDA: J4.3, J6.6; also elsewhere on the board
I2C_SCL_5V: J5.4; also elsewhere on the board
I2C_SDA_5V: J5.3; also elsewhere on the board
unnamed: C38.1, J3.S1 (SHIELD)
SPI1_CS1: J7.9; also elsewhere on the board
SPI1_MISO: J7.5; also elsewhere on the board
SPI1_MOSI: J7.3; also elsewhere on the board
SPI1_SCK: J7.7; also elsewhere on the board
TIM1_CH1: J6.8; also elsewhere on the board
TIM2_CH3: J8.18; also elsewhere on the board
TIM4_CH3: J8.12; also elsewhere on the board
TIM4_CH4: J8.14; also elsewhere on the board
USART1_RX: J6.3; also elsewhere on the board
USART1_TX: J6.4; also elsewhere on the board
USB_CC1: J3.A5 (CC1); also elsewhere on the board
USB_CC2: J3.B5 (CC2); also elsewhere on the board
USB_D+: J3.A6 (D+), J3.B6 (D+), U7.1 (D+); also elsewhere on the board
USB_D-: J3.A7 (D-), J3.B7 (D-), U7.2 (D-); also elsewhere on the board
USB_VBUS: J3.A4 (VBUS), J3.A9 (VBUS), J3.B4 (VBUS), J3.B9 (VBUS); also elsewhere on the board

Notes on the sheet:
EXT_USB
Additional
Sensor
Relay
CAN
Display
Communication

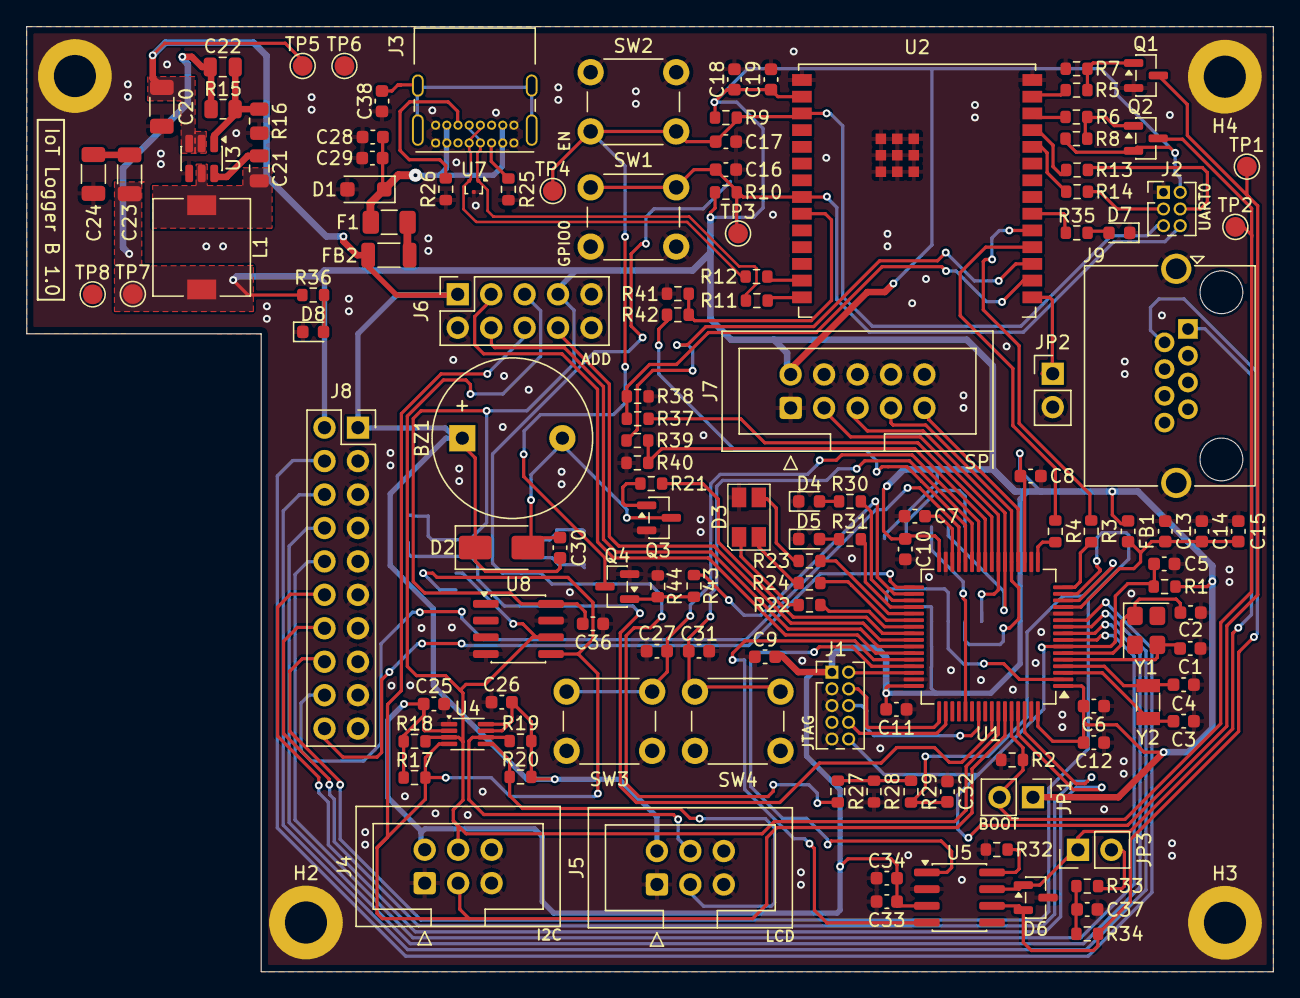
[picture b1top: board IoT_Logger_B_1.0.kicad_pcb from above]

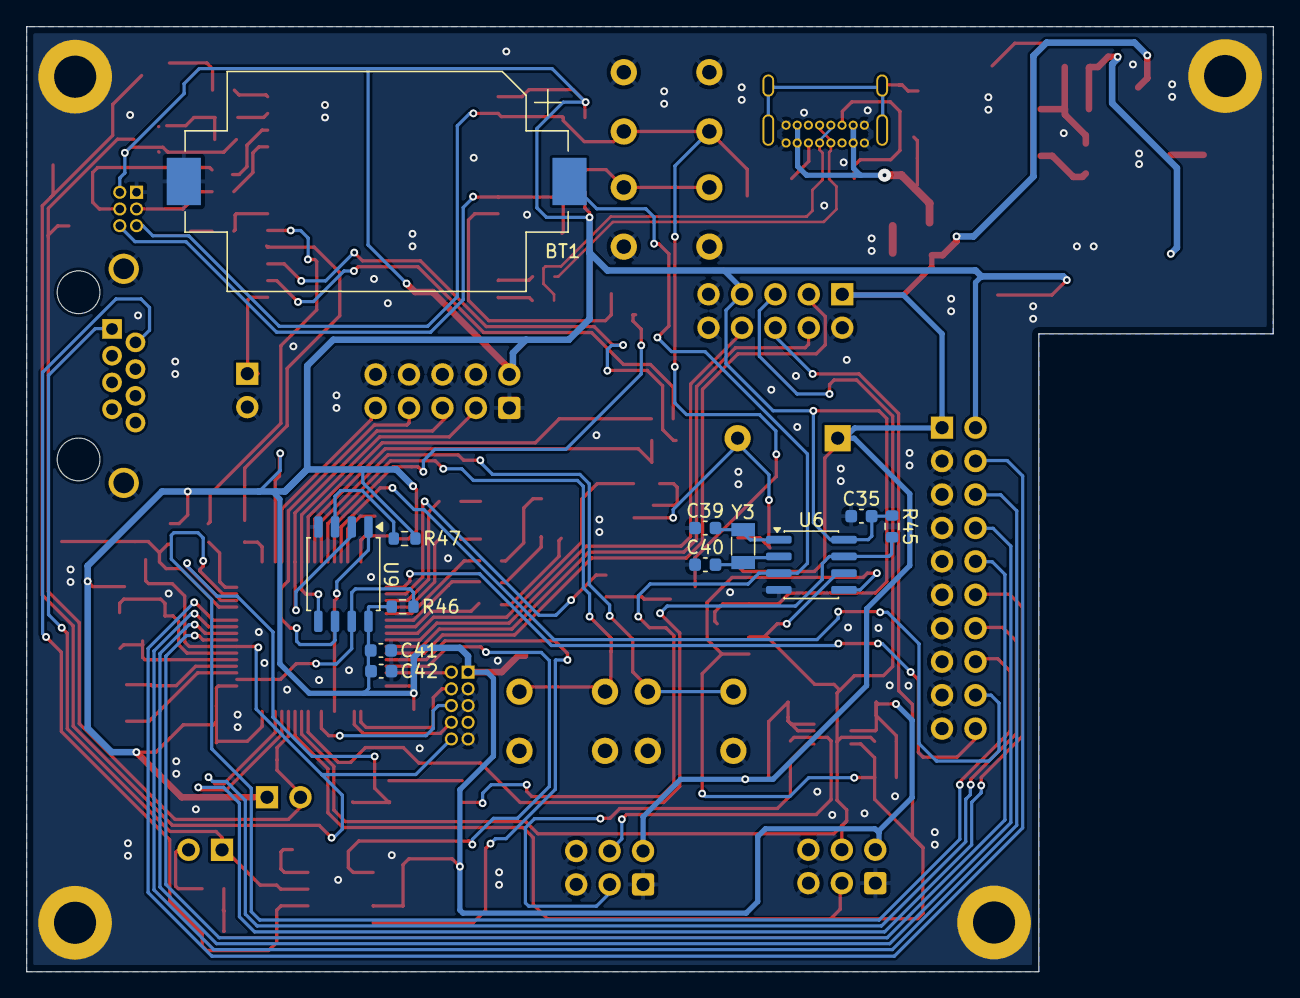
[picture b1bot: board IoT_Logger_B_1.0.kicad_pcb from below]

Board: 2 copper layers, 94.7 x 71.8 mm, 147 parts (12 on the bottom side), 105 nets.
